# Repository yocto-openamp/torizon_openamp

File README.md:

# torizon_openamp

Minimal with NXP i.MX 8M Plus Computer on Module, zephyr and openamp

## Index

* Hardware
  * [Overview](README_hardware_10_overview.md)
  * [Second ETH](README_hardware_30_second_ETH.md)
  * [Networking](README_hardware_40_networking.md)

* Yocto
  * [Overview](README_yocto_10_overview.md)
  * [Prepare build environment](README_yocto_20_prepare_build_environment.md)
  * [How the productxy layer was added](README_yocto_30_add_layer.md)
  * [Build](README_yocto_40_build.md)
  * [Deploy - Tezi Installer](README_yocto_50_deploy_tezi.md)
  * [Deploy - TorizonCoreBuilder](README_yocto_55_deploy_torizon-core-build.md)

## Repositories involved

See [https://github.com/yocto-openamp](https://github.com/yocto-openamp).

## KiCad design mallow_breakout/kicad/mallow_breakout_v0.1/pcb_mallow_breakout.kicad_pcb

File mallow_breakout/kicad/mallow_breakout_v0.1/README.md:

# Mellow Breakout History

## History v0.1.0 -> 

* Solder bridge, 100nF parallel to C217
* Silkscreen: 5V/150ms (5V/15ms without bridge)

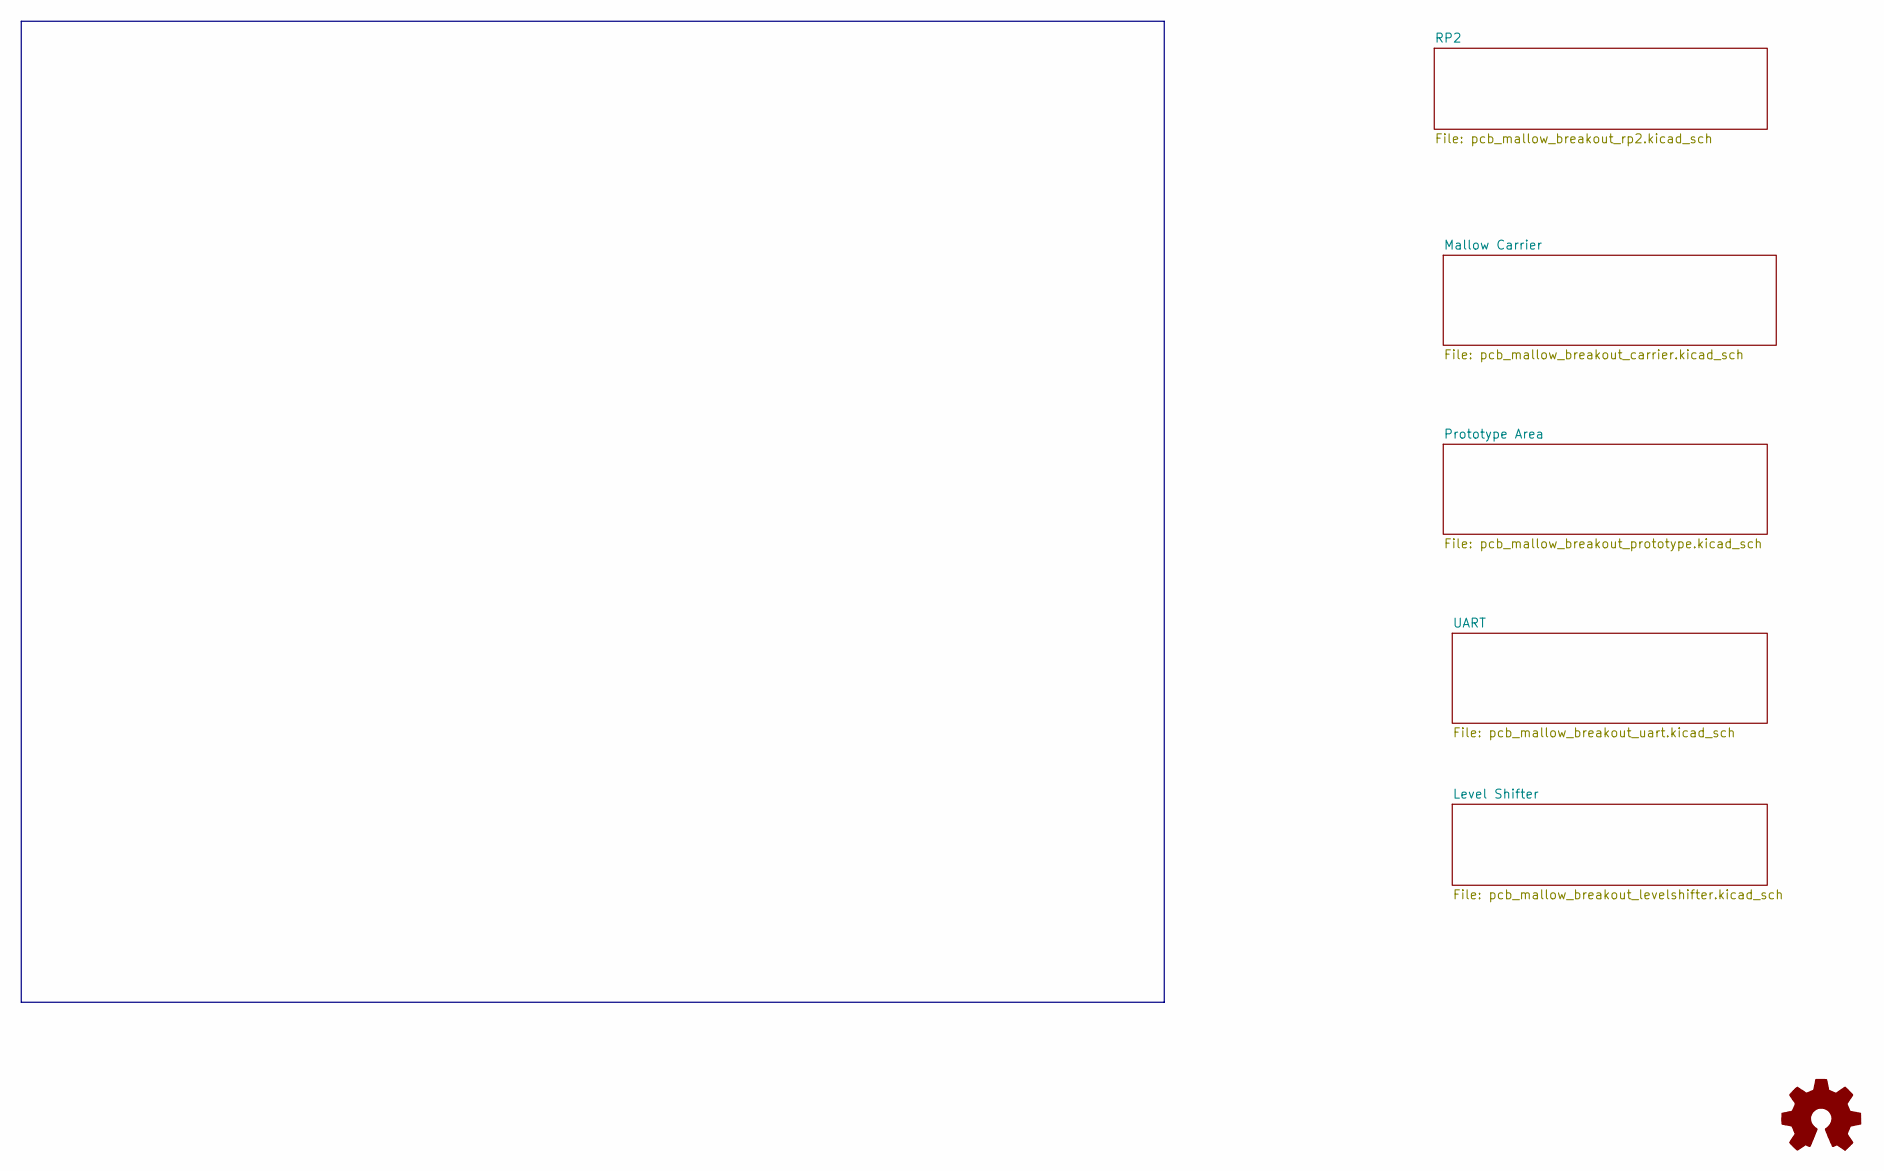
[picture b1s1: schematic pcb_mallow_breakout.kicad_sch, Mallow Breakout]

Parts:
Logo_open_hardware101: Logo_Open_Hardware_Small; OSHW-Logo2_9.8x8mm_SilkScreen

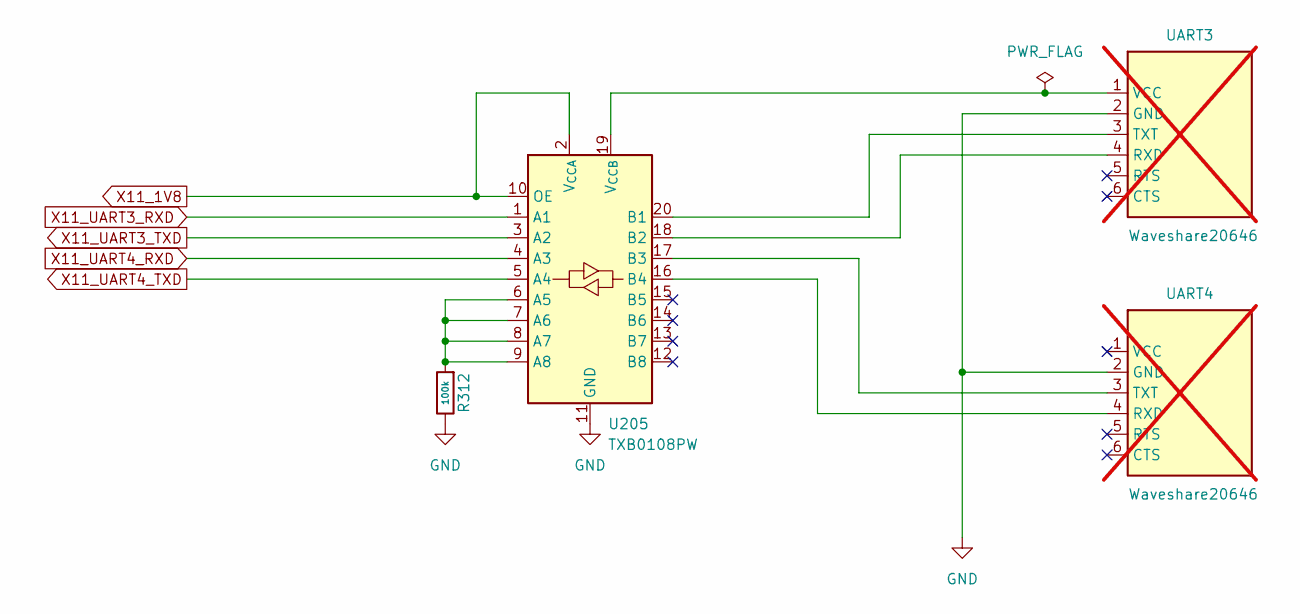
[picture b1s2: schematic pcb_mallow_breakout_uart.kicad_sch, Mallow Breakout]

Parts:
R312: 100k; R_0805_2012Metric
U205: TXB0108PW; TSSOP-20_4.4x6.5mm_P0.65mm; JLC C53406
UART3, UART4: Waveshare20646; not fitted

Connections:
GND: R312.1, U205.11 (GND), UART3.2 (GND), UART4.2 (GND); also elsewhere on the board
unnamed: R312.2, U205.6 (A5), U205.7 (A6), U205.8 (A7), U205.9 (A8)
unnamed: U205.20 (B1), UART3.3 (TXT)
unnamed: U205.18 (B2), UART3.4 (RXD)
unnamed: U205.17 (B3), UART4.3 (TXT)
unnamed: U205.16 (B4), UART4.4 (RXD)
unnamed: U205.19 (V_{CCB}), UART3.1 (VCC)
X11_1V8: U205.2 (V_{CCA}), U205.10 (OE); also elsewhere on the board
X11_UART3_RXD: U205.1 (A1); also elsewhere on the board
X11_UART3_TXD: U205.3 (A2); also elsewhere on the board
X11_UART4_RXD: U205.4 (A3); also elsewhere on the board
X11_UART4_TXD: U205.5 (A4); also elsewhere on the board

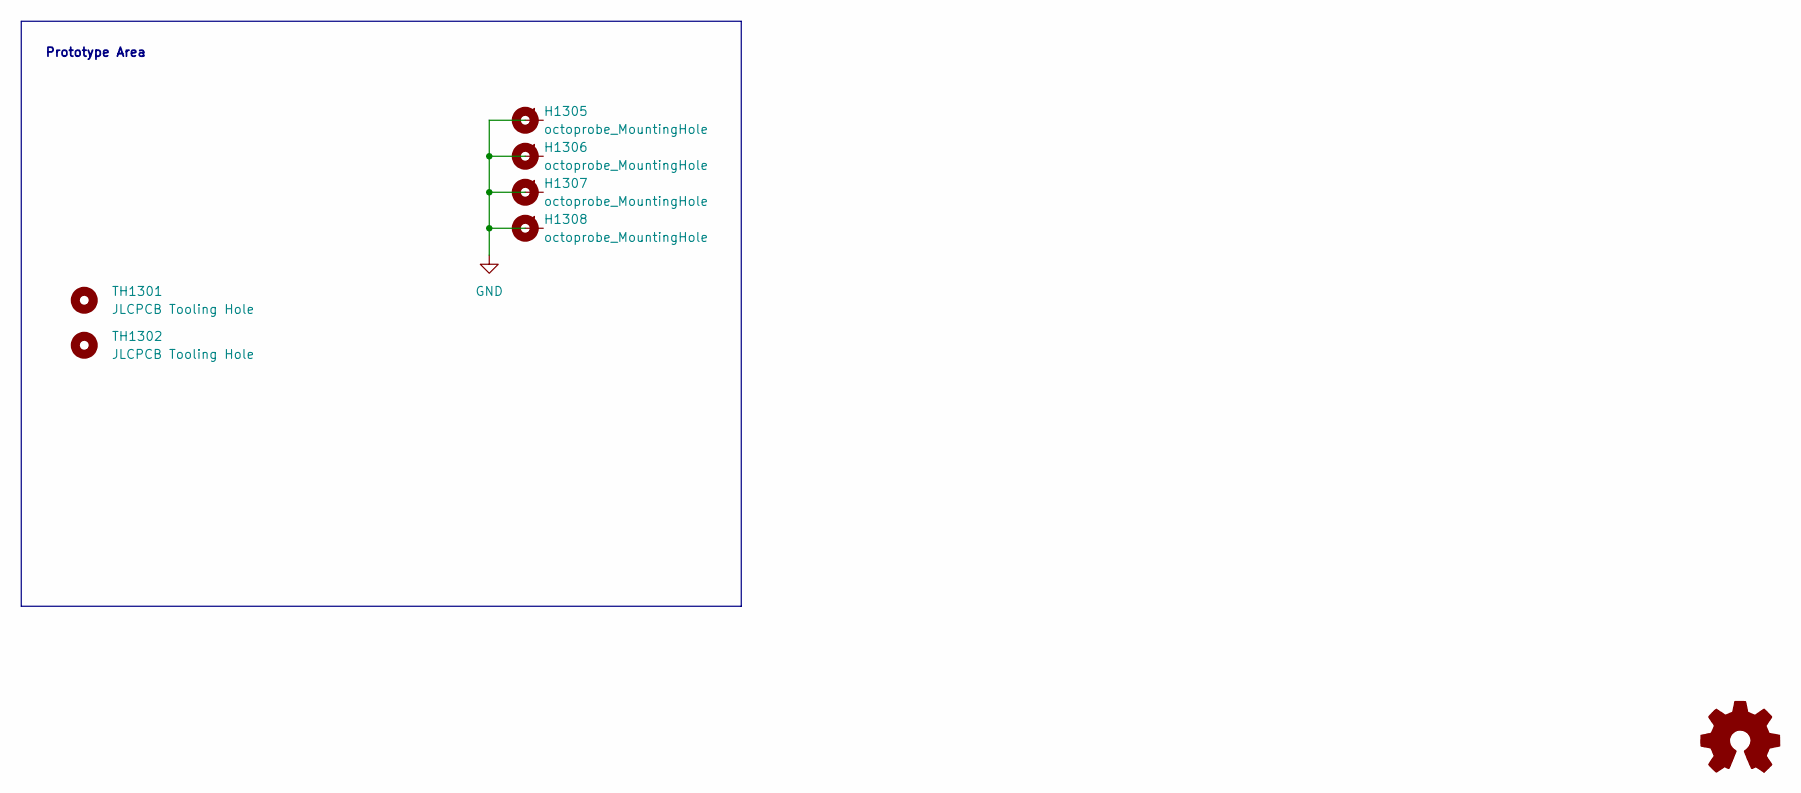
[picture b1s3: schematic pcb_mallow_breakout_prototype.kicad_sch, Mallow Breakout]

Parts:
H1305, H1306, H1307, H1308: octoprobe_MountingHole; MountingHole_3.2mm_M3_DIN965_Pad
TH1301, TH1302: JLCPCB Tooling Hole; JLCPCB_ToolingHole

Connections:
GND: H1305.1, H1306.1, H1307.1, H1308.1; also elsewhere on the board

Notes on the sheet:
Prototype Area

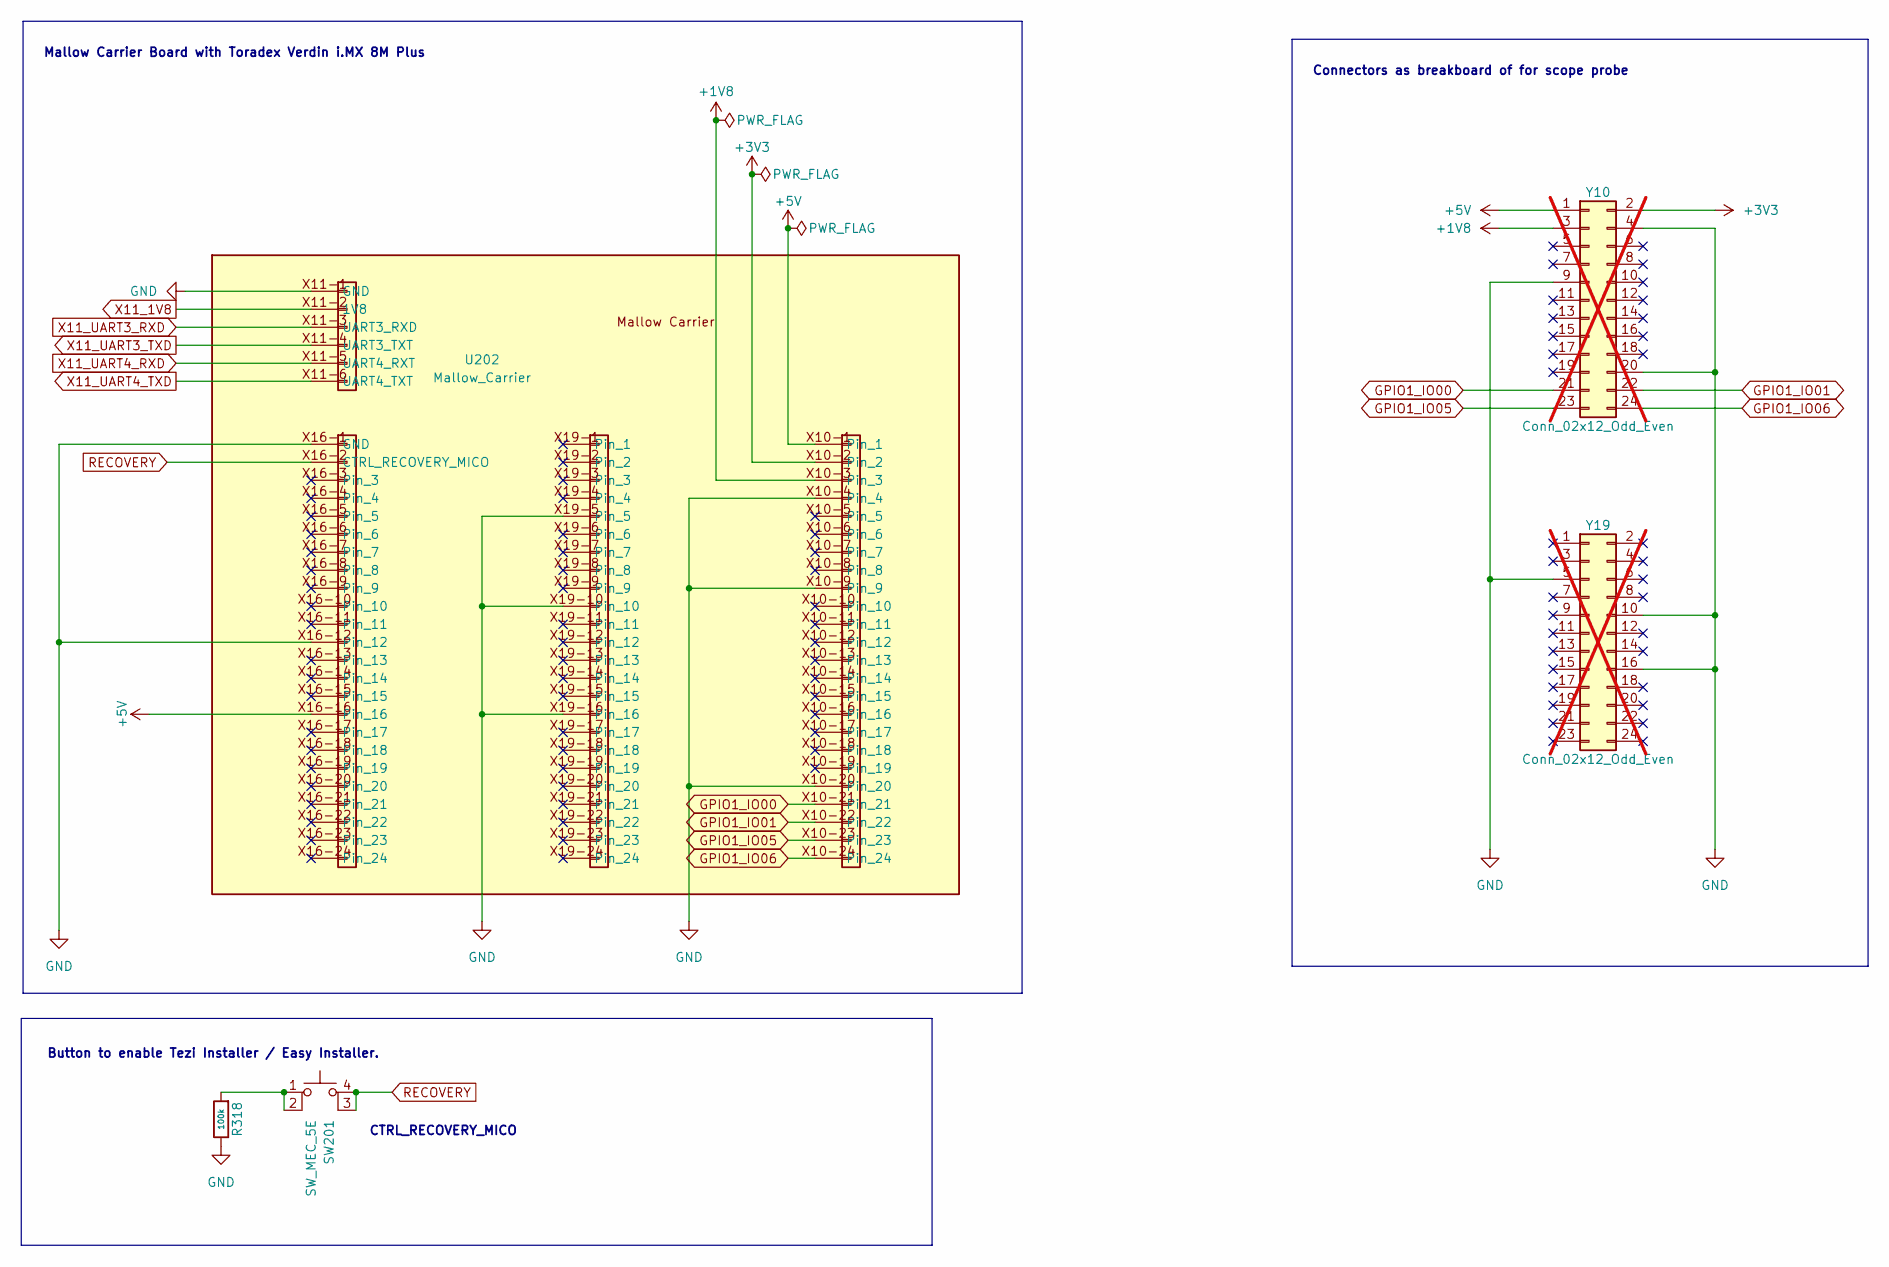
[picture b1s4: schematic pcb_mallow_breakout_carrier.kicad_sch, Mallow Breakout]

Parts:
R318: 100k; R_0805_2012Metric
SW201: SW_MEC_5E; SW_TS-1187A-B-A-B; JLC C318884
U202: Mallow_Carrier
Y10, Y19: Conn_02x12_Odd_Even; PinHeader_2x12_P2.54mm_Vertical_Mirror; not fitted

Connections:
+1V8: U202.X10-3 (Pin_3), Y10.3; also elsewhere on the board
+3V3: U202.X10-2 (Pin_2), Y10.2
+5V: U202.X10-1 (Pin_1), U202.X16-16 (Pin_16), Y10.1
GND: R318.1, U202.X10-4 (Pin_4), U202.X10-9 (Pin_9), U202.X10-20 (Pin_20), U202.X11-1 (GND), U202.X16-1 (GND), U202.X16-12 (Pin_12), U202.X19-5 (Pin_5), U202.X19-10 (Pin_10), U202.X19-16 (Pin_16), Y10.4, Y10.9, Y10.20, Y19.5, Y19.10, Y19.16; also elsewhere on the board
GPIO1_IO00: U202.X10-21 (Pin_21), Y10.21; also elsewhere on the board
GPIO1_IO01: U202.X10-22 (Pin_22), Y10.22; also elsewhere on the board
GPIO1_IO05: U202.X10-23 (Pin_23), Y10.23; also elsewhere on the board
GPIO1_IO06: U202.X10-24 (Pin_24), Y10.24; also elsewhere on the board
unnamed: R318.2, SW201.1, SW201.2
RECOVERY: SW201.3 (K), SW201.4 (A), U202.X16-2 (CTRL_RECOVERY_MICO)
X11_1V8: U202.X11-2 (1V8); also elsewhere on the board
X11_UART3_RXD: U202.X11-3 (UART3_RXD); also elsewhere on the board
X11_UART3_TXD: U202.X11-4 (UART3_TXT); also elsewhere on the board
X11_UART4_RXD: U202.X11-5 (UART4_RXT); also elsewhere on the board
X11_UART4_TXD: U202.X11-6 (UART4_TXT); also elsewhere on the board

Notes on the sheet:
Mallow Carrier Board with Toradex Verdin i.MX 8M Plus
Connectors as breakboard of for scope probe
Button to enable Tezi Installer / Easy Installer.
CTRL_RECOVERY_MICO

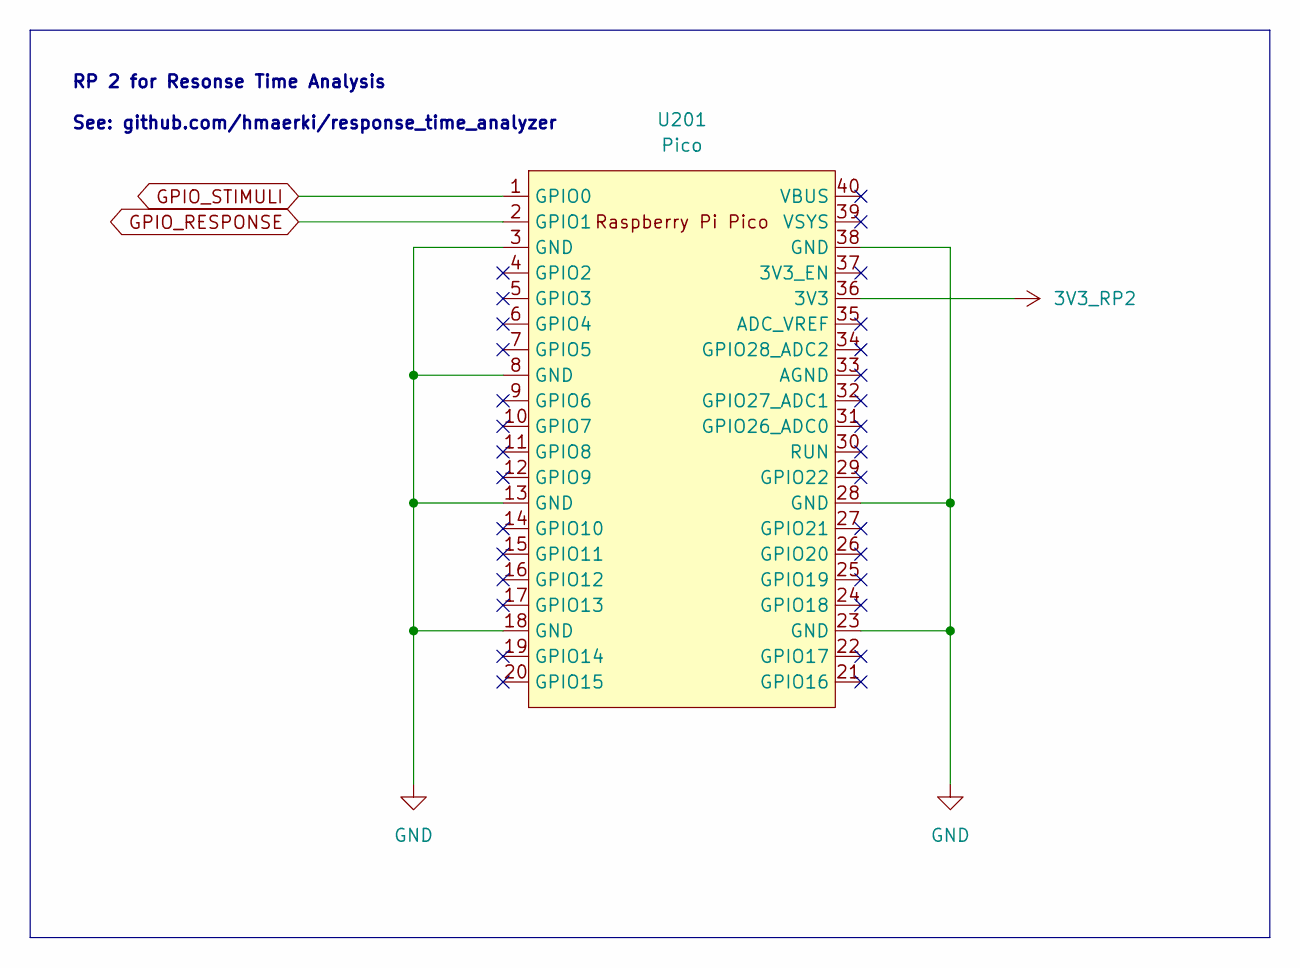
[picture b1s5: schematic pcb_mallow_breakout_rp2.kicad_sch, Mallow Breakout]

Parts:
U201: Pico; RPi_Pico

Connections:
3V3_RP2: U201.36 (3V3); also elsewhere on the board
GND: U201.3 (GND), U201.8 (GND), U201.13 (GND), U201.18 (GND), U201.23 (GND), U201.28 (GND), U201.38 (GND); also elsewhere on the board
GPIO_RESPONSE: U201.2 (GPIO1); also elsewhere on the board
GPIO_STIMULI: U201.1 (GPIO0); also elsewhere on the board

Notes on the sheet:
RP 2 for Resonse Time Analysis See: github.com/hmaerki/response_time_analyzer

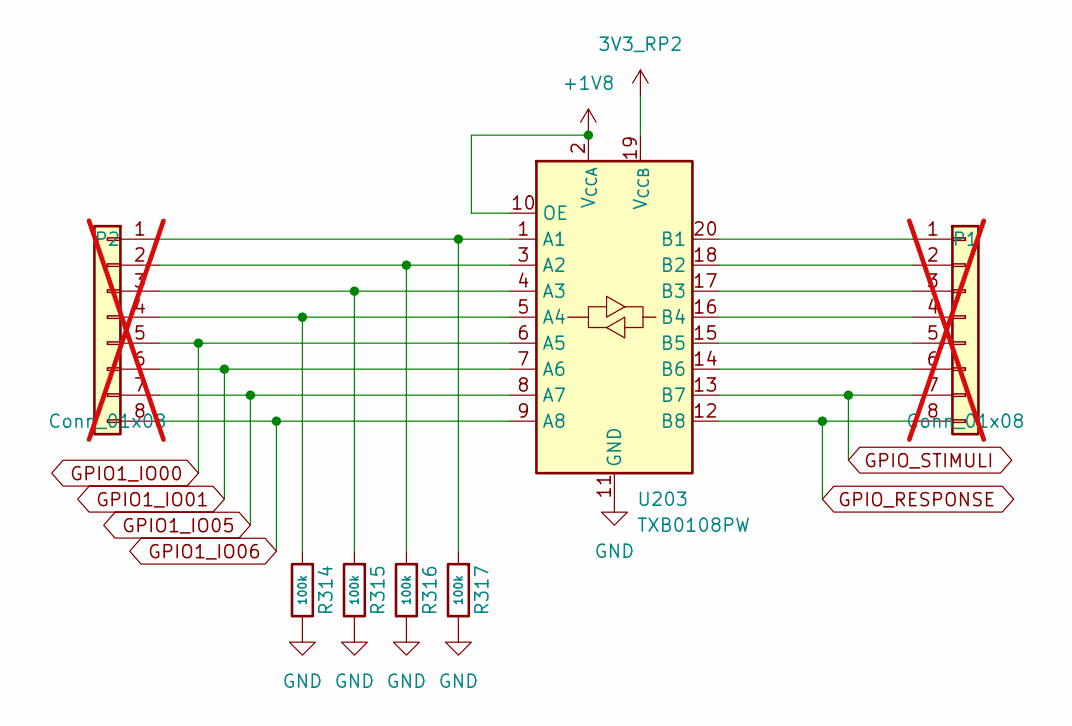
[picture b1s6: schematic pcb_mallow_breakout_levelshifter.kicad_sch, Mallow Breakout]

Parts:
P1, P2: Conn_01x08; PinHeader_1x08_P2.54mm_Vertical; not fitted
R314, R315, R316, R317: 100k; R_0805_2012Metric
U203: TXB0108PW; TSSOP-20_4.4x6.5mm_P0.65mm; JLC C53406

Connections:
3V3_RP2: U203.19 (V_{CCB}); also elsewhere on the board
+1V8: U203.2 (V_{CCA}), U203.10 (OE); also elsewhere on the board
GND: R314.1, R315.1, R316.1, R317.1, U203.11 (GND); also elsewhere on the board
GPIO1_IO00: P2.5, U203.6 (A5); also elsewhere on the board
GPIO1_IO01: P2.6, U203.7 (A6); also elsewhere on the board
GPIO1_IO05: P2.7, U203.8 (A7); also elsewhere on the board
GPIO1_IO06: P2.8, U203.9 (A8); also elsewhere on the board
GPIO_RESPONSE: P1.8, U203.12 (B8); also elsewhere on the board
GPIO_STIMULI: P1.7, U203.13 (B7); also elsewhere on the board
unnamed: P1.1, U203.20 (B1)
unnamed: P1.2, U203.18 (B2)
unnamed: P1.3, U203.17 (B3)
unnamed: P1.4, U203.16 (B4)
unnamed: P1.5, U203.15 (B5)
unnamed: P1.6, U203.14 (B6)
unnamed: P2.1, R317.2, U203.1 (A1)
unnamed: P2.2, R316.2, U203.3 (A2)
unnamed: P2.3, R315.2, U203.4 (A3)
unnamed: P2.4, R314.2, U203.5 (A4)

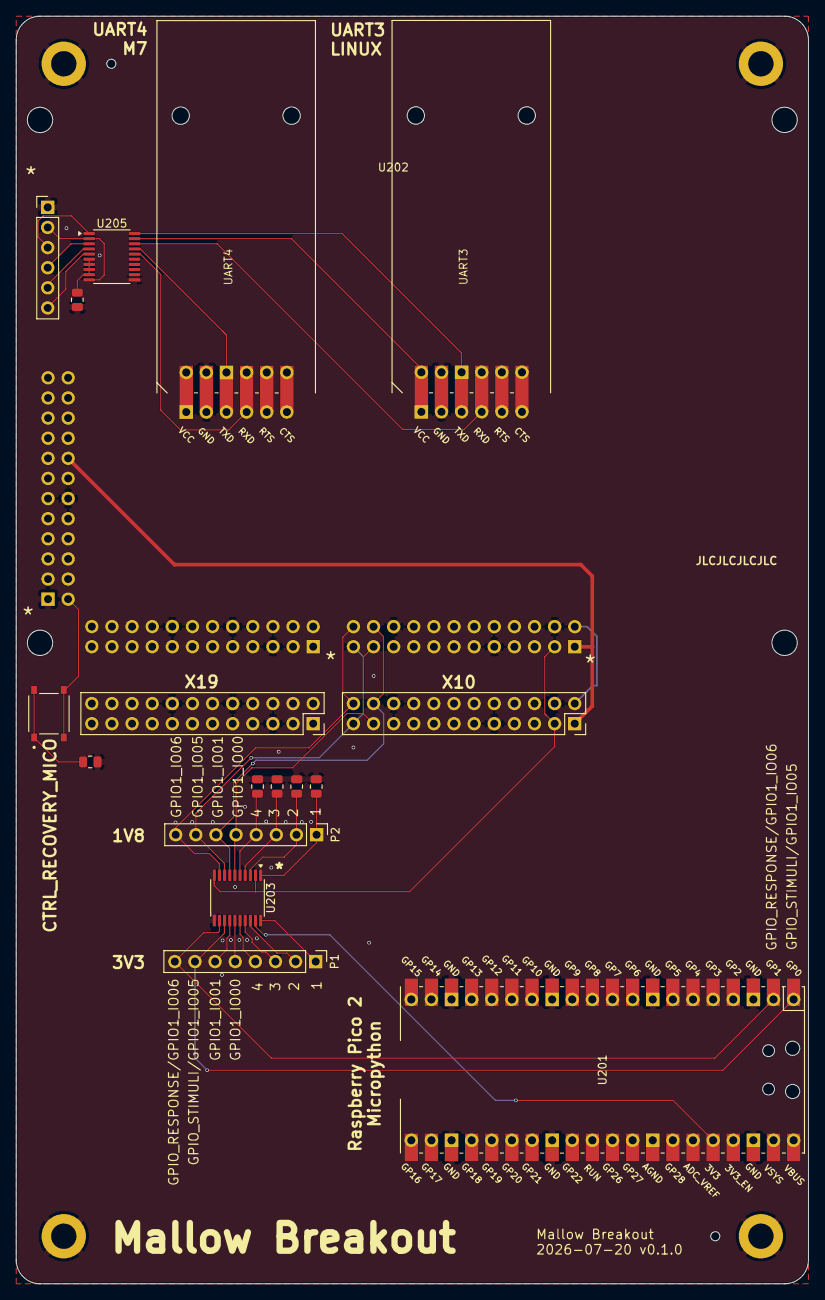
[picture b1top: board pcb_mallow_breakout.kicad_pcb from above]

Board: 2 copper layers, 100.0 x 160.0 mm, 24 parts (1 on the bottom side), 34 nets.

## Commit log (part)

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2026-06-01 projectxy -> productxy
2026-06-01 README_add_layer_productxy.md
2026-06-02 Document how to add and build layer_productxy
2026-06-05 Updated some readmes
2026-06-06 Implement tezi_server

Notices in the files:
mallow_breakout/kicad/mallow_breakout_v0.1/pcb_mallow_breakout.kicad_pcb:
The MIT License (MIT)
